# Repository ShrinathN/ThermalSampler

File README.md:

# ThermalSampler

Wireless thermal logger. Intended use is to help in thermally modelling a room.

Sensor nodes made using an STM32G0 MCU and connectivity options include

* nRF24L01+
* RFM95W/CW/TW
* RFM96W/TW

Sleep current is ~2uA

Aggregator is a simple ESP32 based dev board connected to nRF24L01+ (PA breakout board) in my case.

# Fully assembled

# PCB

# Enclosure

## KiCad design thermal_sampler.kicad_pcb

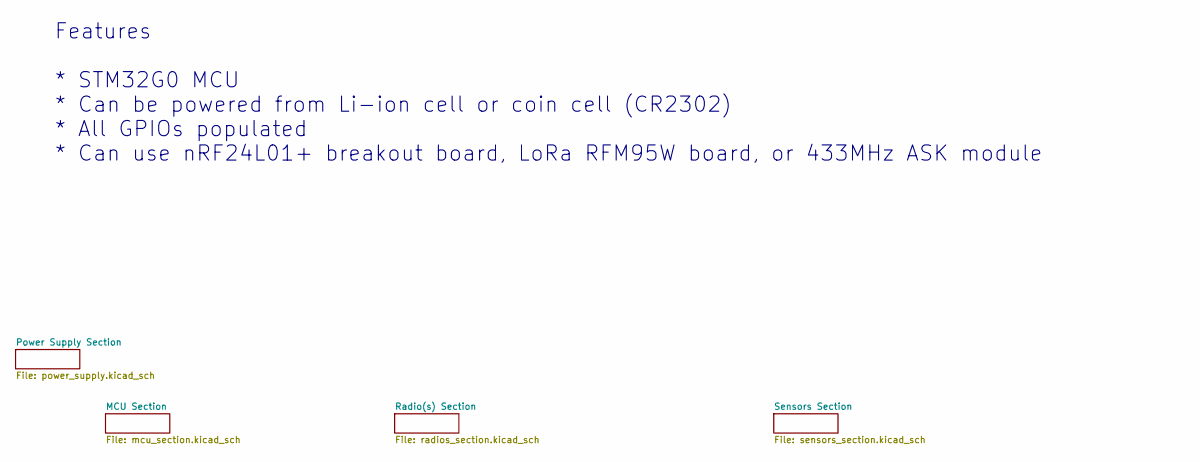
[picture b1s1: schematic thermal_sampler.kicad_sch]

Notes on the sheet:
Features * STM32G0 MCU * Can be powered from Li-ion cell or coin cell (CR2302) * All GPIOs populated * Can use nRF24L01+ breakout board, LoRa RFM95W board, or 433MHz ASK module

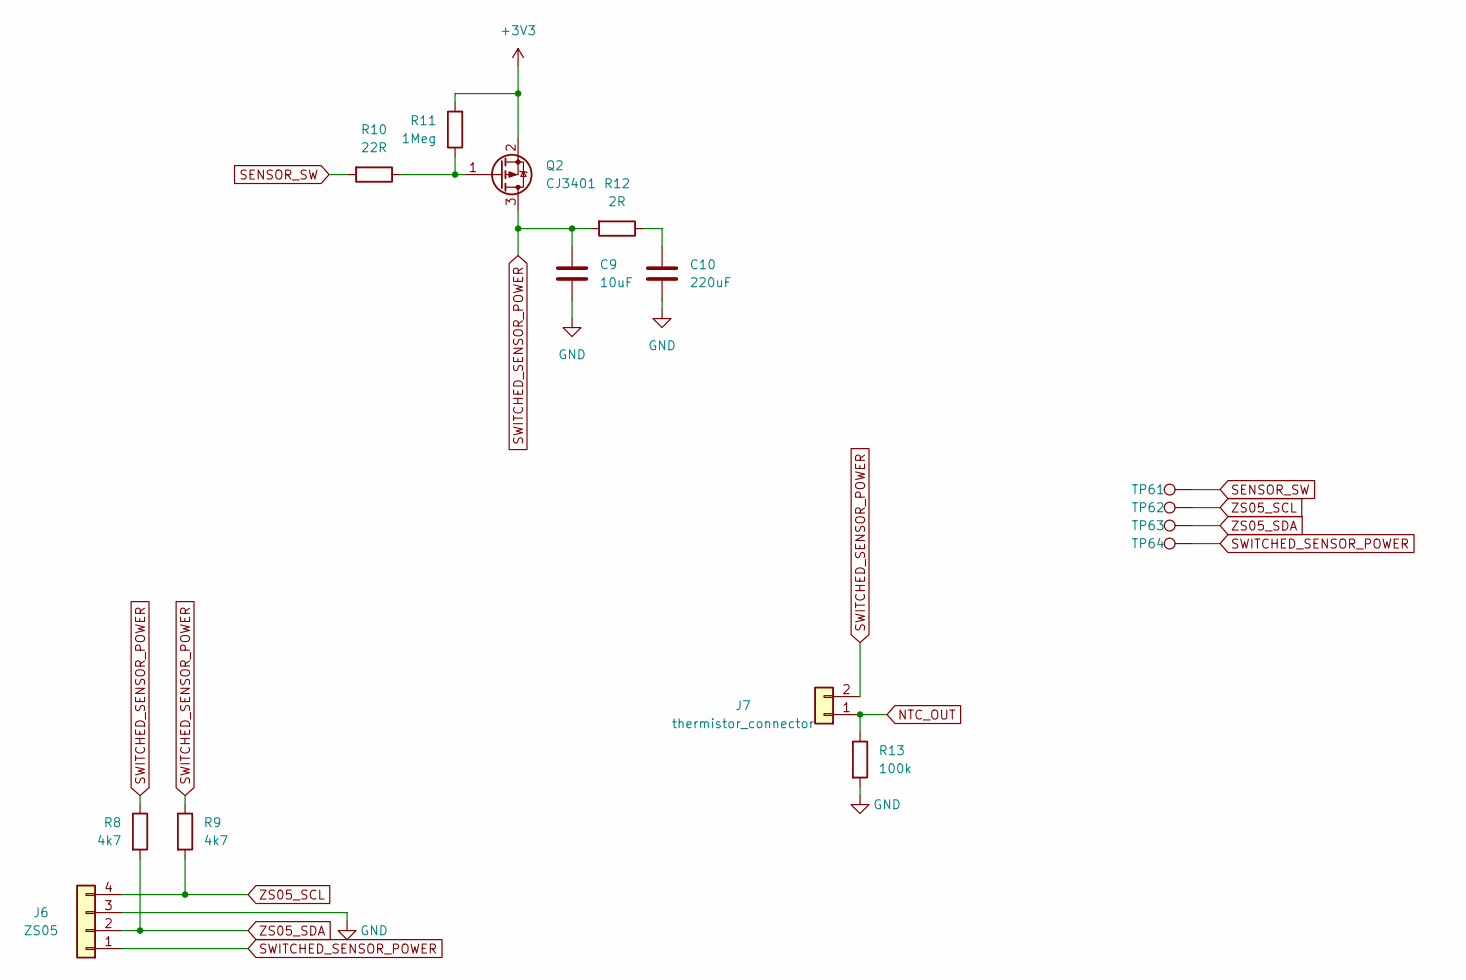
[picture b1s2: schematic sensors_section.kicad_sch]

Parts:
C9: 10uF; C_0805_2012Metric
C10: 220uF; C_Radial_D6.3mm_H11.0mm_P2.50mm
J6: ZS05; Conn_01x04
J7: thermistor_connector; Conn_01x02
Q2: CJ3401; SOT-23
R8, R9: 4k7; R_0805_2012Metric
R10: 22R; R_0805_2012Metric
R11: 1Meg; R_0805_2012Metric
R12: 2R; R_1206_3216Metric
R13: 100k; R_0805_2012Metric
TP61, TP62, TP63, TP64: TestPoint; TestPoint_Pad_D1.0mm

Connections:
+3V3: Q2.2 (S), R11.2; also elsewhere on the board
GND: C9.2, C10.2, J6.3, R13.2; also elsewhere on the board
NTC_OUT: J7.1, R13.1; also elsewhere on the board
unnamed: C10.1, R12.1
unnamed: Q2.1 (G), R10.1, R11.1
SENSOR_SW: R10.2, TP61.1; also elsewhere on the board
SWITCHED_SENSOR_POWER: C9.1, J6.1, J7.2, Q2.3 (D), R8.1, R9.1, R12.2, TP64.1
ZS05_SCL: J6.4, R9.2, TP62.1; also elsewhere on the board
ZS05_SDA: J6.2, R8.2, TP63.1; also elsewhere on the board

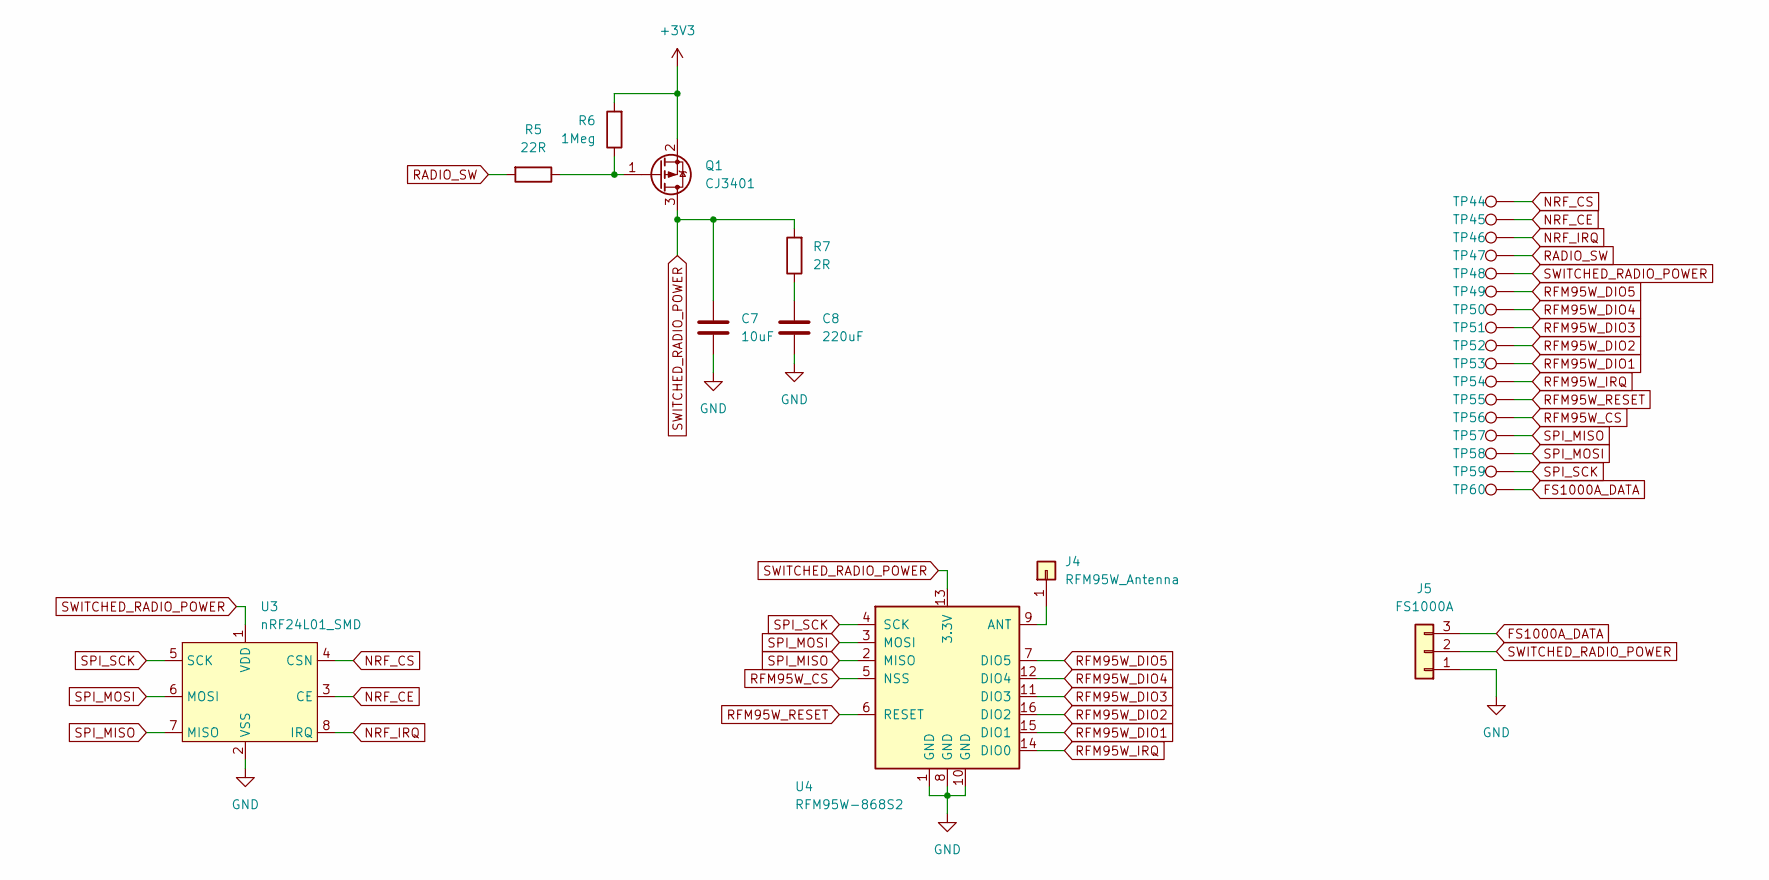
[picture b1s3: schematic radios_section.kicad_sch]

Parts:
C7: 10uF; C_0805_2012Metric
C8: 220uF; C_Radial_D6.3mm_H11.0mm_P2.50mm
J4: RFM95W_Antenna; Conn_01x01
J5: FS1000A; Conn_01x03
Q1: CJ3401; SOT-23
R5: 22R; R_0805_2012Metric
R6: 1Meg; R_0805_2012Metric
R7: 2R; R_1206_3216Metric
TP44, TP45, TP46, TP47, TP48, TP49, TP50, TP51, TP52, TP53, TP54, TP55, TP56, TP57, TP58, TP59, TP60: TestPoint; TestPoint_Pad_D1.0mm
U3: nRF24L01_SMD
U4: RFM95W-868S2; HOPERF_RFM9XW_SMD

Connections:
+3V3: Q1.2 (S), R6.2; also elsewhere on the board
FS1000A_DATA: J5.3, TP60.1; also elsewhere on the board
GND: C7.2, C8.2, J5.1, U3.2 (VSS), U4.1 (GND), U4.8 (GND), U4.10 (GND); also elsewhere on the board
NRF_CE: TP45.1, U3.3 (CE); also elsewhere on the board
NRF_CS: TP44.1, U3.4 (CSN); also elsewhere on the board
NRF_IRQ: TP46.1, U3.8 (IRQ); also elsewhere on the board
unnamed: C8.1, R7.1
unnamed: J4.1, U4.9 (ANT)
unnamed: Q1.1 (G), R5.1, R6.1
RADIO_SW: R5.2, TP47.1; also elsewhere on the board
RFM95W_CS: TP56.1, U4.5 (NSS); also elsewhere on the board
RFM95W_DIO1: TP53.1, U4.15 (DIO1)
RFM95W_DIO2: TP52.1, U4.16 (DIO2)
RFM95W_DIO3: TP51.1, U4.11 (DIO3)
RFM95W_DIO4: TP50.1, U4.12 (DIO4)
RFM95W_DIO5: TP49.1, U4.7 (DIO5)
RFM95W_IRQ: TP54.1, U4.14 (DIO0); also elsewhere on the board
RFM95W_RESET: TP55.1, U4.6 (RESET); also elsewhere on the board
SPI_MISO: TP57.1, U3.7 (MISO), U4.2 (MISO); also elsewhere on the board
SPI_MOSI: TP58.1, U3.6 (MOSI), U4.3 (MOSI); also elsewhere on the board
SPI_SCK: TP59.1, U3.5 (SCK), U4.4 (SCK); also elsewhere on the board
SWITCHED_RADIO_POWER: C7.1, J5.2, Q1.3 (D), R7.2, TP48.1, U3.1 (VDD), U4.13 (3.3V)

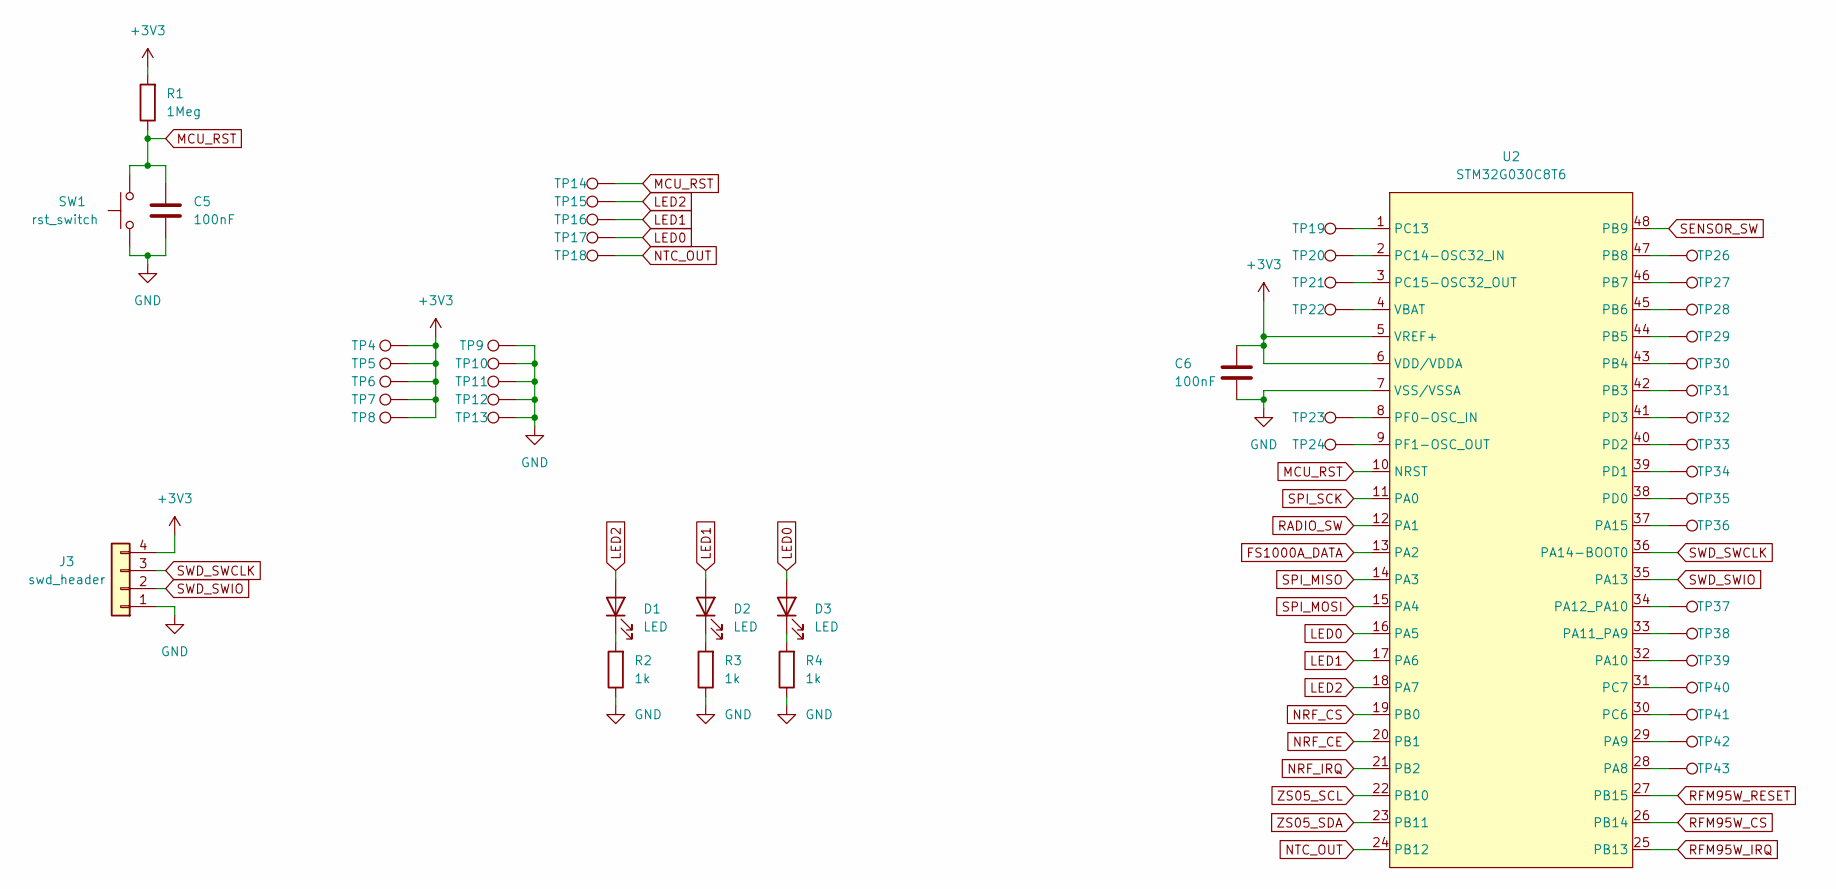
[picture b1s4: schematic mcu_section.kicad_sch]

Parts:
C5, C6: 100nF; C_0805_2012Metric
D1, D2, D3: LED; LED_1206_3216Metric
J3: swd_header; Conn_01x04
R1: 1Meg; R_0805_2012Metric
R2, R3, R4: 1k; R_0805_2012Metric
SW1: rst_switch; SW_SPST_TL3342
TP4, TP5, TP6, TP7, TP8, TP9, TP10, TP11, TP12, TP13, TP14, TP15, TP16, TP17, TP18, TP19, TP20, TP21, TP22, TP23, TP24, TP26, TP27, TP28, TP29, TP30, TP31, TP32, TP33, TP34, TP35, TP36, TP37, TP38, TP39, TP40, TP41, TP42, TP43: TestPoint; TestPoint_Pad_D1.0mm
U2: STM32G030C8T6; LQFP-48_7x7mm_P0.5mm

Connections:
+3V3: C6.1, J3.4, R1.2, TP4.1, TP5.1, TP6.1, TP7.1, TP8.1, U2.5 (VREF+), U2.6 (VDD/VDDA); also elsewhere on the board
FS1000A_DATA: U2.13 (PA2); also elsewhere on the board
GND: C5.1, C6.2, J3.1, R2.1, R3.1, R4.1, SW1.1, TP9.1, TP10.1, TP11.1, TP12.1, TP13.1, U2.7 (VSS/VSSA); also elsewhere on the board
LED0: D3.2 (A), TP17.1, U2.16 (PA5)
LED1: D2.2 (A), TP16.1, U2.17 (PA6)
LED2: D1.2 (A), TP15.1, U2.18 (PA7)
MCU_RST: C5.2, R1.1, SW1.2, TP14.1, U2.10 (NRST)
NRF_CE: U2.20 (PB1); also elsewhere on the board
NRF_CS: U2.19 (PB0); also elsewhere on the board
NRF_IRQ: U2.21 (PB2); also elsewhere on the board
NTC_OUT: TP18.1, U2.24 (PB12); also elsewhere on the board
unnamed: D1.1 (K), R2.2
unnamed: D2.1 (K), R3.2
unnamed: D3.1 (K), R4.2
unnamed: TP19.1, U2.1 (PC13)
unnamed: TP20.1, U2.2 (PC14-OSC32_IN)
unnamed: TP21.1, U2.3 (PC15-OSC32_OUT)
unnamed: TP22.1, U2.4 (VBAT)
unnamed: TP23.1, U2.8 (PF0-OSC_IN)
unnamed: TP24.1, U2.9 (PF1-OSC_OUT)
unnamed: TP26.1, U2.47 (PB8)
unnamed: TP27.1, U2.46 (PB7)
unnamed: TP28.1, U2.45 (PB6)
unnamed: TP29.1, U2.44 (PB5)
unnamed: TP30.1, U2.43 (PB4)
unnamed: TP31.1, U2.42 (PB3)
unnamed: TP32.1, U2.41 (PD3)
unnamed: TP33.1, U2.40 (PD2)
unnamed: TP34.1, U2.39 (PD1)
unnamed: TP35.1, U2.38 (PD0)
unnamed: TP36.1, U2.37 (PA15)
unnamed: TP37.1, U2.34 (PA12_PA10)
unnamed: TP38.1, U2.33 (PA11_PA9)
unnamed: TP39.1, U2.32 (PA10)
unnamed: TP40.1, U2.31 (PC7)
unnamed: TP41.1, U2.30 (PC6)
unnamed: TP42.1, U2.29 (PA9)
unnamed: TP43.1, U2.28 (PA8)
RADIO_SW: U2.12 (PA1); also elsewhere on the board
RFM95W_CS: U2.26 (PB14); also elsewhere on the board
RFM95W_IRQ: U2.25 (PB13); also elsewhere on the board
RFM95W_RESET: U2.27 (PB15); also elsewhere on the board
SENSOR_SW: U2.48 (PB9); also elsewhere on the board
SPI_MISO: U2.14 (PA3); also elsewhere on the board
SPI_MOSI: U2.15 (PA4); also elsewhere on the board
SPI_SCK: U2.11 (PA0); also elsewhere on the board
SWD_SWCLK: J3.3, U2.36 (PA14-BOOT0)
SWD_SWIO: J3.2, U2.35 (PA13)
ZS05_SCL: U2.22 (PB10); also elsewhere on the board
ZS05_SDA: U2.23 (PB11); also elsewhere on the board

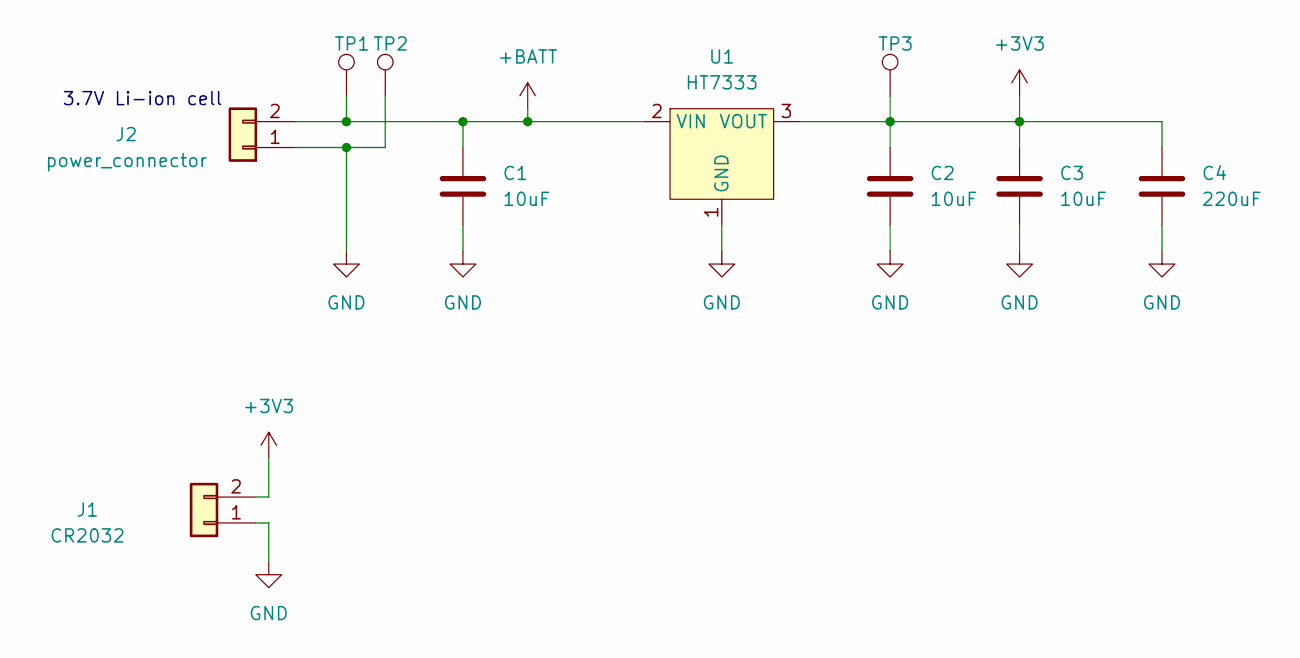
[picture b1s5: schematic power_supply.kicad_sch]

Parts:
C1, C2, C3: 10uF; C_0805_2012Metric
C4: 220uF; C_Radial_D6.3mm_H11.0mm_P2.50mm
J1: CR2032; CR2032_THT
J2: power_connector; PinHeader_1x02_P2.54mm_Vertical
TP1, TP2, TP3: TestPoint; TestPoint_Pad_D1.0mm
U1: HT7333; SOT-89-3

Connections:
+3V3: C2.1, C3.1, C4.1, J1.2, TP3.1, U1.3 (VOUT); also elsewhere on the board
+BATT: C1.1, J2.2, TP1.1, U1.2 (VIN)
GND: C1.2, C2.2, C3.2, C4.2, J1.1, J2.1, TP2.1, U1.1 (GND); also elsewhere on the board

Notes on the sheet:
3.7V Li-ion cell

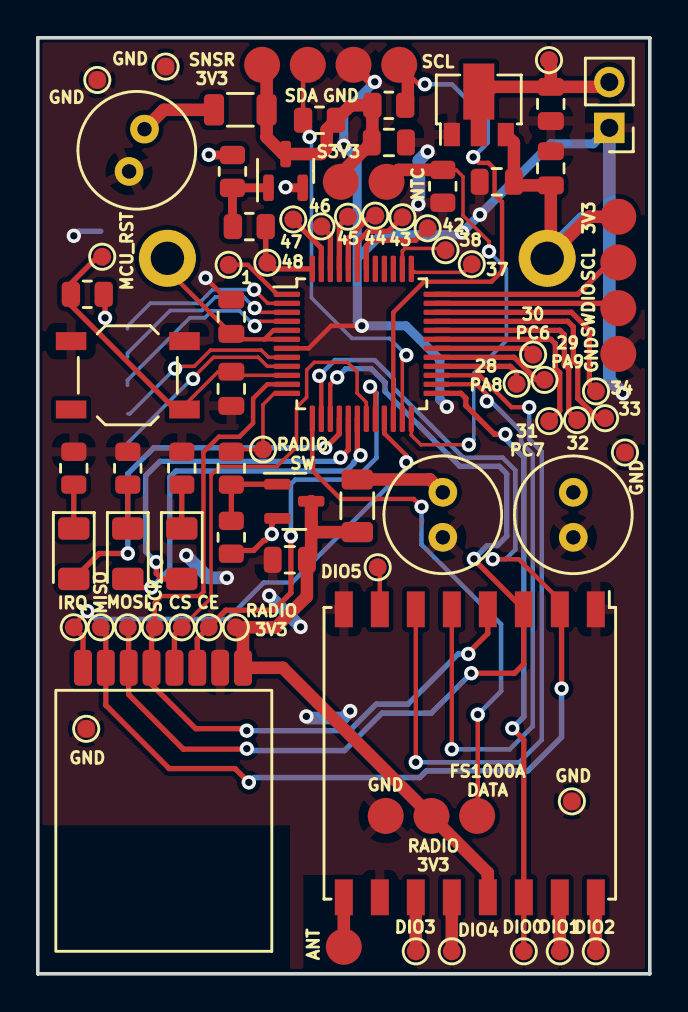
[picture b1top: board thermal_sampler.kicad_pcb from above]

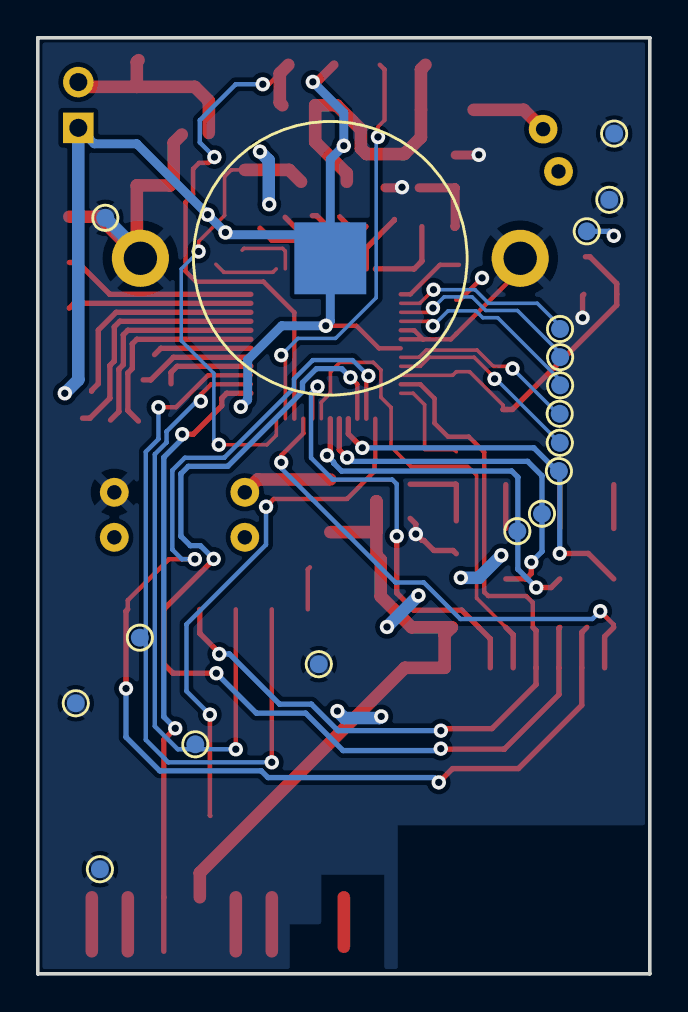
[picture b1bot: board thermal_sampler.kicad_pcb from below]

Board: 2 copper layers, 34.0 x 52.0 mm, 95 parts (18 on the bottom side), 60 nets.

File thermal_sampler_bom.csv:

Item,Qty,Reference(s),Value,LibPart,Footprint,Datasheet,For 5 boards
1,5,"C1, C2, C3, C7, C9",10uF,Device:C,Capacitor_SMD:C_0805_2012Metric,~,25
2,3,"C4, C8, C10",220uF,Device:C,Capacitor_THT:C_Radial_D6.3mm_H11.0mm_P2.50mm,~,15
3,2,"C5, C6",100nF,Device:C,Capacitor_SMD:C_0805_2012Metric,~,10
4,3,"D1, D2, D3",LED,Device:LED,LED_SMD:LED_1206_3216Metric,~,15
5,1,J1,CR2032,Connector_Generic:Conn_01x02,CR2032_THT:CR2032_THT,~,5
6,1,J2,power_connector,Connector_Generic:Conn_01x02,Connector_PinHeader_2.54mm:PinHeader_1x02_P2.54mm_Vertical,~,5
7,1,J3,swd_header,Connector_Generic:Conn_01x04,smd_footprint:Conn_01x04,~,5
8,1,J4,RFM95W_Antenna,Connector_Generic:Conn_01x01,smd_footprint:Conn_01x01,~,5
9,1,J5,FS1000A,Connector_Generic:Conn_01x03,smd_footprint:Conn_01x03,~,5
10,1,J6,ZS05,Connector_Generic:Conn_01x04,smd_footprint:Conn_01x04,~,5
11,1,J7,thermistor_connector,Connector_Generic:Conn_01x02,smd_footprint:Conn_01x02,~,5
12,2,"Q1, Q2",CJ3401,Device:Q_PMOS_GSD,Package_TO_SOT_SMD:SOT-23,~,10
13,3,"R1, R6, R11",1Meg,Device:R,Resistor_SMD:R_0805_2012Metric,~,15
14,3,"R2, R3, R4",1k,Device:R,Resistor_SMD:R_0805_2012Metric,~,15
15,2,"R5, R10",22R,Device:R,Resistor_SMD:R_0805_2012Metric,~,10
16,2,"R7, R12",2R,Device:R,Resistor_SMD:R_1206_3216Metric,~,10
17,2,"R8, R9",4k7,Device:R,Resistor_SMD:R_0805_2012Metric,~,10
18,1,R13,100k,Device:R,Resistor_SMD:R_0805_2012Metric,~,5
19,1,SW1,rst_switch,Switch:SW_Push,Button_Switch_SMD:SW_SPST_TL3342,~,5
20,1,U1,HT7333,HT7333:HT7333,Package_TO_SOT_SMD:SOT-89-3,https://datasheet.lcsc.com/szlcsc/Holtek-Semicon-HT7333-A_C2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,5
21,1,U2,STM32G030C8T6,STM32G030C8T6:STM32G030C8T6,Package_QFP:LQFP-48_7x7mm_P0.5mm,,5
22,1,U3,nRF24L01_SMD,nrf24l01_smd:nRF24L01_SMD,nRF24L01_SMD:nRF24L01_SMD,,5
23,1,U4,RFM95W-868S2,RF_Module:RFM95W-868S2,RF_Module:HOPERF_RFM9XW_SMD,https://www.hoperf.com/data/upload/portal/20181127/5bfcbea20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,5

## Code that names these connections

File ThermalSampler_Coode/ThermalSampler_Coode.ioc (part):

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Mcu.Name=STM32G030C(6-8)Tx
Mcu.Package=LQFP48
Mcu.UserName=STM32G030C8Tx
PA0.Mode=Full_Duplex_Master
PA0.Signal=SPI2_SCK
PA1.GPIOParameters=PinState,GPIO_Label
PA1.GPIO_Label=RADIO_SW
PA1.PinState=GPIO_PIN_SET
PA1.Signal=GPIO_Output
PA12\ [PA10].GPIOParameters=GPIO_PuPd,GPIO_Label
PA12\ [PA10].GPIO_Label=PROG_EN
PA12\ [PA10].GPIO_PuPd=GPIO_PULLUP
PA12\ [PA10].Signal=GPIO_Input
PA13.Mode=Serial_Wire
PA13.Signal=SYS_SWDIO
PA14-BOOT0.Mode=Serial_Wire
PA14-BOOT0.Signal=SYS_SWCLK
PA2.GPIOParameters=GPIO_Label
PA2.GPIO_Label=FS1000A_DATA
PA2.Mode=Half_duplex(single_wire_mode)
PA2.Signal=USART2_TX
PA3.Mode=Full_Duplex_Master
PA3.Signal=SPI2_MISO
PA4.Mode=Full_Duplex_Master
PA4.Signal=SPI2_MOSI
PA5.GPIOParameters=GPIO_Label
PA5.GPIO_Label=LED0
PA5.Signal=GPIO_Output
PA6.GPIOParameters=GPIO_Label
PA6.GPIO_Label=LED1
PA6.Signal=GPIO_Output
PA7.GPIOParameters=GPIO_Label
PA7.GPIO_Label=LED2
PA7.Signal=GPIO_Output
PB0.GPIOParameters=GPIO_Label
PB0.GPIO_Label=NRF_CS
PB0.Signal=GPIO_Output
PB1.GPIOParameters=GPIO_Label
PB1.GPIO_Label=NRF_CE
PB1.Signal=GPIO_Output
PB10.Mode=I2C
PB10.Signal=I2C2_SCL
PB11.Mode=I2C
PB11.Signal=I2C2_SDA
PB12.GPIOParameters=GPIO_Label
PB12.GPIO_Label=NTC_THERMISTOR
PB12.Signal=SharedAnalog_PB12
PB13.GPIOParameters=GPIO_Label
PB13.GPIO_Label=RFM95W_IRQ
PB13.Signal=GPXTI13
PB14.GPIOParameters=PinState,GPIO_Label
PB14.GPIO_Label=RFM95W_CS
PB14.PinState=GPIO_PIN_SET
PB14.Signal=GPIO_Output
PB15.GPIOParameters=GPIO_Label
PB15.GPIO_Label=RFM95W_RESET
PB15.Signal=GPIO_Output
PB2.GPIOParameters=GPIO_Label,GPIO_ModeDefaultEXTI
PB2.GPIO_Label=NRF_IRQ
PB2.GPIO_ModeDefaultEXTI=GPIO_MODE_IT_FALLING
PB2.Signal=GPXTI2
PB9.GPIOParameters=PinState,GPIO_Label
PB9.GPIO_Label=SENSOR_SW
PB9.PinState=GPIO_PIN_SET
PB9.Signal=GPIO_Output
RCC.HSE_VALUE=8000000
RCC.SYSCLKFreq_VALUE=2000000
board=custom

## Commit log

2023-05-26 Added files
